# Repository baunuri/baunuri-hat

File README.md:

# Baunuri HAT

A robot controller board the size of a Raspberry Pi HAT (65 × 57 mm, the Pi's hole pattern and 40-pin header), built
around an ESP32-S3. It runs a robot on its own, or sits on a Pi when a robot needs more compute.

It was designed for [Popm](https://baunuri.com/popm/) and now also runs [XL-Duck](https://baunuri.com/xlduck/), whose
trained walking network runs on the ESP32-S3 itself. More: [baunuri.com/hat](https://baunuri.com/hat/).

## On the board
- **MCU:** ESP32-S3-WROOM-1-N16R8 (16 MB flash, 8 MB PSRAM), native USB-C for flashing and logs
- **Servos:** two half-duplex TTL servo bus plugs (Feetech STS3215 pinout), powered straight from the battery
- **RS485** (SP3485, UART0, DE on a GPIO) and **CAN** (SN65HVD230), each with a terminator behind a solder jumper
- **IMU:** LSM6DS3TR-C
- **Sound:** MAX98357A I2S amp, speaker plug
- **microSD** (SPI), **TCA9555** 16-bit I/O expander, two I2C buses (sensor plugs, ToF plug, Qwiic)
- **Power:** 2S–4S battery in (XT30), reverse-polarity FET, fuse, TVS; 5.4 V / 2 A buck, 3.3 V LDO; battery voltage sense
- **Pi header:** UART to the Pi, the Pi can reset the ESP32 or put it into its bootloader; the Pi's 5 V can run the logic,
  the battery never feeds the Pi

Full spec, pin map, power budget and design notes: [`pcb/README.md`](pcb/README.md). Pin map in code:
[`firmware/hat_bringup/board_hat.h`](firmware/hat_bringup/board_hat.h).

## Status
**Rev A**, ordered assembled from JLCPCB in November 2026 and brought up: the bring-up sketch
(`firmware/hat_bringup/`) tests each part over USB. An STS3215 runs on the servo bus at 1 Mbps (position within ~0.4°,
286°/s peak once its acceleration limit, register 85, is raised from the factory 50). XL-Duck's servos run on the RS485
port at 1 Mbps.

## Files
| Path | What |
|---|---|
| `pcb/popm_board.py` | the schematic, as code ([SKiDL](https://github.com/devbisme/skidl)) → netlist |
| `pcb/popm_board.kicad_pcb` | the layout (KiCad 9) |
| `pcb/layout.py`, `route.py`, `stitch.py`, `silk.py`, … | placement / routing / stitching / silkscreen scripts |
| `pcb/fab/` | what was ordered: Gerbers (zip), BOM and placement (CPL) for JLCPCB assembly, schematic PDF |
| `firmware/hat_bringup/` | the pin map (`board_hat.h`) and a bring-up sketch (Arduino, ESP32 core) |

## Making one
Upload `pcb/fab/popm_gerbers.zip` to JLCPCB with `popm_bom.csv` and `popm_cpl.csv` for assembly. **4 layers, 1.6 mm,
1 oz outer and 1 oz inner copper** (not the 0.5 oz inner default). The 2 × 20 Pi socket (J13) isn't in the BOM: solder a
tall stacking header yourself if you'll use a Pi. Check the notes in `pcb/README.md` ("Check by hand") first.

Or get a ready-made one: see [baunuri.com/hat](https://baunuri.com/hat/#get-one).

## Licenses
- **Hardware** (`pcb/`): [CERN-OHL-S-2.0](LICENSE), strongly reciprocal: if you make and distribute a modified board,
  publish its design files under the same licence.
- **Firmware** (`firmware/`): [MIT](firmware/LICENSE).
- **Documentation and images:** [CC BY 4.0](LICENSE-docs).

"Baunuri" and "Baunuri HAT" are names, not covered by these licences: boards you make from these files are welcome, but
please don't sell them under those names.

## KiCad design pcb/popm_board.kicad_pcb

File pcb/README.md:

# Design notes: Baunuri HAT rev A (POPM-HAT)

The board: the same circuits as the 74 × 38 POPM-CTRL, on a Raspberry Pi HAT-size board (65 × 57 mm, the Pi's
hole pattern) with a Pi-style 2 × 20 header (HATs plug onto it), a microSD on SPI and a 16-bit I2C GPIO expander.

One board instead of the Waveshare ESP32 servo board, the GY-521, the MAX98357A breakout, the buck converter and the
charge diode. It also adds a connector for the 8×8 ToF sensor.

**Status:** schematic as code (`popm_board.py`, SKiDL; ERC clean, 81 nets, 120 parts), placed, routed and through the
fab gate (`fab.py`); reviewed; ordered from JLCPCB (assembled) on 2026-11-10 at commit a57b8a4.

    cd pcb && python3 -m venv .venv && .venv/bin/pip install skidl   # once; needs KiCad 9's libraries
    .venv/bin/python popm_board.py                                    # -> popm_board.net (import it in Pcbnew)

## Fit
- **Outline:** 65 × 57 mm, rounded corners (R 3). 4 × 3.0 mm NPTH holes (M2.5) at (3.5, 4), (61.5, 4), (3.5, 53), (61.5, 53)
  from the top-left corner: a 58 × 49 mm rectangle, as on a Pi / HAT. No copper within 3.0 mm of a hole's centre, either side
  (screw heads, standoffs). 4 layers, 1.6 mm: F / In1 (solid GND) / In2 (signals) / B.
- **Order:** 4 layers, 1.6 mm, 1 oz outer **and 1 oz inner copper** (not JLC's 0.5 oz inner default: the battery trunk may run on the inner layer). Assemble 2, everything included: JLC solders the through-hole plugs too (`HAND=1` leaves them off and writes an LCSC cart instead).
- **Edges:** top: the Pi header (female, underneath). Left: the ESP32-S3's antenna over a notch (no copper beside it). Bottom: USB-C, I2C_B1, I2C_B2, QWIIC, TOF
  (JST-SH mouths at the edge). Right: BATTERY (XT30), UART (JST-SH), microSD slot. SERVO1/2 and SPEAKER are
  vertical plugs inside.
- **Stack height on a Pi 5:** use a tall stacking header with 15-16 mm (or taller) spacers. On a standard 8.5 mm or a low-profile socket the microSD card and the XT30 lead run into the Pi 5's Ethernet / USB jacks (review, from the Pi 5 drawing).
- **On a Pi:** this board is a HAT: it plugs onto a Raspberry Pi's 40-pin header with a female 2 × 20 socket underneath,
  and its holes line up with the Pi's (M2.5 standoffs). The socket's height sets the gap: underside parts and the plugs'
  through-hole pins (~2–3 mm) must clear the Pi's own parts (not checked against any Pi model).

## Pi header (J13, 2 × 20, 2.54 mm, female, underneath). Each pad right over the Pi's pin: rows at y 4 ± 1.27, pin 1 inside, at the left end
**Not assembled by JLC:** solder a tall 2 × 20 stacking header (2.54 mm, female, for 15-16 mm spacers on a Pi 5) yourself, from underneath (fab.py leaves J13 off the order).
The Pi and the ESP32 never drive the same line: everything else on the header is left open.
| Pi pin | Pi name | Net | This board |
|---|---|---|---|
| 2, 4 | 5V | PI_5V | into our +5V through a Schottky (D8): the Pi can run the ESP side; our battery never feeds the Pi |
| 6, 9, 14, 20, 25, 30, 34, 39 | GND | GND | |
| 8 | TXD (Pi out) | PI_TXD → 1k → UART_RX | ESP GPIO40 (UART2 RX) |
| 10 | RXD (Pi in) | UART_TX → 1k → PI_RXD | ESP GPIO39 (UART2 TX) |
| 11 | GPIO17 | PI_EN → 2N7002 (Q3) → ESP EN | Pi high = ESP held in reset |
| 13 | GPIO27 | PI_BOOT → 2N7002 (Q4) → ESP GPIO0 | Pi high = ESP boots into download mode (with a reset) |
| 7, 15, 16, 18, 22, 26, 29, 31 | | EXP_P00 … EXP_P07 (expander port 0, in that order) | |
| 32, 33, 36, 37 | | EXP_P10 … EXP_P13 (expander port 1) | |
| 1, 17 (3V3), 3, 5 (I2C), 27, 28 (ID EEPROM), 12, 35, 38, 40 (PCM), 19, 21, 23, 24 (SPI) | | not connected | |

- **UART2 is shared with the UART plug (J12):** use the Pi link or a device on the plug, not both (two TX outputs on one RX).
  The 1k resistors stop either side back-powering the other while it's off.
- **Reset / boot from the Pi:** the FETs (100k gate pull-downs; the Pi's GPIO17 / 27 also pull down at boot) stay off while the
  Pi is off or booting. Flash the ESP from the Pi over a USB-C cable (its ROM loader's UART is UART0, the RS485 one).
- **The 12 expander lines** come up as inputs on both sides (TCA9555 and the Pi): set directions in software before driving any.

## GPIO expander (U9, TCA9555PWR, LCSC C465732)
- On I2C bus A (I2C_A_SDA / I2C_A_SCL) at **0x20** (A0-A2 to GND; the IMU is 0x6A, the ToF 0x29). 3V3, 100 nF at VCC.
- P00-P07 and P10-P13 go to the header (table above). P14 / P15: AUX_EN / AUX_BOOT (UART plug; Pi pins 11 / 13 are PI_EN / PI_BOOT: the Pi resets / boot-selects the ESP), P16: the ToF's LPn, P17: test pad TP8.
- **INT is not wired to the ESP32** (no free GPIO): it has a 10k pull-up and test pad TP9. Firmware polls the input registers.

## microSD (J14, Molex 104031-0811, LCSC C585350), SPI mode
- DAT3/CS → SD_CS (GPIO 13), CMD → SPI_MOSI (38), CLK → SPI_SCK (21), DAT0 → SPI_MISO (47). 10k pull-ups to 3V3 on CS, CMD,
  DAT0, DAT1, DAT2; 10 µF + 100 nF at VDD. The card-detect switch isn't wired.
- Slot at the right edge. It's a push-pull socket (the card slides in and is pulled out), not push-push.

## CAN (U10, SN65HVD230, LCSC C12084) and RS485 (U11, SP3485EN, LCSC C8963)
- **CAN:** the ESP32-S3's TWAI on GPIO 41 (TX → D) / 42 (RX ← R). Rs to GND (full speed). 10k pull-up on TX: recessive
  through reset. Plug J15 (JST-GH 4, DroneCAN order): 1 +5V, 2 CANH, 3 CANL, 4 GND.
- **RS485:** UART0 (GPIO 43 TX → DI, 44 RX ← RO; the console is on USB), DE + /RE together on GPIO 8 (high = send), 10k
  pull-down: receiving through reset, so the boot log never reaches the bus. Plug J16 (JST-GH 4): 1 +5V, 2 A, 3 B, 4 GND.
- Each: a 120R terminator behind a solder jumper (JP1 CAN, JP2 RS485: bridge it on the boards at the bus's two ends) and a
  TVS (PESD2CAN, SM712). No RS485 fail-safe bias resistors: add them on the bus if nothing else biases it.

## Blocks
```
 2S–4S pack ───────────── reverse-polarity P-FET ─ fuse ─ TVS ─┬─ VBAT ── 2 × servo bus connectors (STS3215 chains)
                   │                                      └─ buck 5.4 V / 2 A ─ SS34 ─┬─ +5 V ── amp, XIAO, LED
                                                               USB-C VBUS ─ SS34 ──────┘    └─ AMS1117 ── +3V3: ESP32-S3, IMU, eyes, ToF, buffer
 (no switch, no charge port: in the pack's own lead)           VBAT divider ─▶ ADC

 ESP32-S3-WROOM-1-N16R8 ── UART1 ── 74LVC2G241 (DIR) ── servo bus (half duplex)
                        ── I2C bus B (up to 1 MHz) ── I2C_B1, I2C_B2 plugs, e.g. displays (JST-SH 4)
                        ── I2C bus A (400 kHz max) ── IMU + expander on board, ToF (JST-SH 6), Qwiic (JST-SH 4)
                        ── I2S ── MAX98357A ── speaker (JST-PH 2)
                        ── UART2 + EN/BOOT ── XIAO camera (JST-SH 6)
                        ── USB-C (native USB: flash + log, 5 V for the logic on the bench)
                        ── red status LED (GPIO48, high = on), BOOT button (doubles as a user button)
```

## Parts (LCSC numbers to fill in while drawing the schematic: prefer JLC basic / preferred parts)
| Block | Part | Why |
|---|---|---|
| MCU | ESP32-S3-WROOM-1-N16R8 | 16 MB flash (no more 97 %), 8 MB PSRAM, native USB, 2 I2C, 3 UARTs, I2S |
| Servo bus | 74LVC2G241 at 3.3 V + 10 k pull-up | half duplex with one DIR pin (the Robotis circuit). LVC inputs take 5 V, so a 5 V bus is safe on RX |
| IMU | LSM6DS3TR-C (or BMI270) | the MPU-6050 is end-of-life and clones vary; this one is cheap and stocked at JLC. Firmware: new register map |
| Amp | MAX98357AETE+ | same as now; SD_MODE on a GPIO (mute with no pop, save power) |
| 5 V buck | TPS54202 (4.5–28 V in, 2 A), set to 5.4 V, then an SS34 Schottky OR with USB 5 V | headroom over 12.6 V and charger spikes; USB powers the logic on the bench |
| 3.3 V | AMS1117-3.3 from 5 V | the average draw is ~0.2 A (Wi-Fi peaks are short); a second buck if it runs hot |
| Reverse polarity | P-FET, 30 V, ≥ 8 A (AO4407-class) | the pack plugged in backwards |
| Protection | 5 A / 30 V PTC fuse, SMBJ18A TVS on VBAT, USBLC6-2 on USB | rated for a full 4S (16.8 V); battery-side caps 35 V |
| Sense | VBAT 100 k / 18 k → ADC (16.8 V → 2.56 V) | battery % for the page |

## Pin map (ESP32-S3-WROOM-1-N16R8: GPIO 26–37 are taken by the octal flash and PSRAM)
| Function | GPIO |
|---|---|
| Servo TX / RX / DIR (UART1) | 17 / 18 / 16 |
| I2C bus B SDA / SCL (the two I2C_B plugs) | 4 / 5 |
| I2C bus A SDA / SCL (IMU, ToF, expander, Qwiic): **400 kHz max** (the TCA9555 and the IMU are Fast-mode parts) | 6 / 7 |
| IMU INT | 15 |
| ToF INT (LPn: expander P16) | 14 |
| I2S BCLK / LRC / DIN, amp SD | 10 / 11 / 12, 9 |
| VBAT sense (ADC1) | 1 (IO2 is free: it was the charger-present sense) |
| UART2 TX / RX (UART plug, Pi pins 10 / 8) | 39 / 40 |
| CAN TX / RX (TWAI) | 41 / 42 |
| RS485 TX / RX (UART0) / DE | 43 / 44 / 8 (enable GPIO44's pull-up: RO is high-Z while sending) |
| microSD: MOSI / MISO / SCK / CS | 38 / 47 / 21 / 13 |
| Status LED (red, through 1 k; high = on) | 48 |
| BOOT / user button | 0 |
| USB D− / D+ | 19 / 20 |
| Not connected (straps: JTAG select, flash voltage, ROM log) | 3, 45, 46 |
| On the expander: UART plug EN / BOOT, ToF LPn | P14 / P15, P16 (set the expander's outputs at boot: it keeps them through an ESP reset) |

## Connectors
| What | Connector | Pins |
|---|---|---|
| Battery in | XT30PW-M right angle (the pack's lead is an XT30 female) | pad 2 +, pad 1 − |

**No power switch and no charge port on the board** (as Waveshare's servo HAT): the board is live whenever a pack is
plugged in. Put a switch in the pack's lead if you want one, and charge the pack on its own charger, unplugged.

**The pack must be a protected one (it has a BMS: short-circuit, over-discharge, over-charge).** The board's 5 A fuse only
covers the board itself, and nothing on the board can stop the servos from running the cells flat.
| SERVO1, SERVO2: servo bus × 2 (e.g. a drive chain and a head chain) | Molex SPOX 5267-03A (the STS3215's own plug) | pin 1 DATA, 2 VBAT, 3 GND (as Waveshare's Bus Servo Adapter (A)) |
| I2C_B1, I2C_B2 | JST-SH 4 | 1 GND, 2 3V3, 3 SDA, 4 SCL (Qwiic order; bus B) |
| ToF | JST-SH 6 | 1 GND, 2 3V3, 3 SDA, 4 SCL, 5 LPn, 6 INT |
| Qwiic | JST-SH 4 | 1 GND, 2 3V3, 3 SDA, 4 SCL (bus A) |
| Speaker | JST-PH 2 | |
| UART (a co-processor, e.g. a XIAO camera) | JST-SH 6 | 1 GND, 2 5V, 3 TX, 4 RX, 5 EN, 6 BOOT (EN / BOOT from the expander: open drain by switching its direction) |
| USB-C | 16-pin receptacle | |

## Power budget
| Rail | Loads | Peak |
|---|---|---|
| VBAT (2S 6–8.4 V, 3S 9–12.6 V or 4S up to 16.8 V; the buck turns on above ~5.8 V) | servos straight off the pack, so match their version to it (STS3215 7.4 V on 2S, 12 V on 3S; 4S only with servos rated for it). Sense dividers 100k / 18k: 16.8 V reads 2.56 V. Bigger servo counts: power them from a separate hub, not through this board. Popm: 4 × STS3215 12 V (stall ~2.7 A each; driving 0.2–0.5 A each). Firmware torque limits keep stalls short | fuse 5 A hold, traces ≥ 5 A |
| 5 V | amp ~0.7 A at full volume, XIAO + camera ~0.3 A | ~1.0 A of 2 A (TPS54202), shared with everything on the 5 V plugs (CAN, RS485, UART) |
| 3.3 V | ESP32-S3 Wi-Fi ~0.5 A, ToF ~0.1 A, eyes 2 × 25 mA, IMU, buffer | ~0.2 A average (Wi-Fi peaks are short): an AMS1117 in SOT-223 can't sustain 0.7 A (~1.2 W) |

## 8×8 ToF (VL53L5CX family, ordered 2026-11-04)
- **Connector:** on the sensor I2C bus, not the eyes' (those send ~1 KB frames all the time). Bus A runs at 400 kHz max (the expander and the IMU on it).
- **LPn on a GPIO:** it can be reset, or moved off its default address if a second one is added.
- **Firmware:** its driver uploads ~86 KB of sensor firmware over I2C at every boot (~90 KB of flash): fine with 16 MB.
- **Placement:** probably the chest next to the camera, looking forward and a little down. CAD to follow when it arrives
  (measure the breakout: SparkFun / Pimoroni / generic).

## XIAO link (camera, mic)
- **Wires:** UART2 at 2 Mbps (both ends are S3s), plus the XIAO's EN (reset) and BOOT (GPIO0), driven open-drain by the main S3.
- **Messages:** short text lines, as the drive firmware already does on Serial: from the XIAO `face x y size`,
  `motion`, `loud`; to it `cam on/off`, `snap`. Small, easy to log, and a future brain can listen in.
- **Updating the XIAO through Popm:** the main S3 holds BOOT low and pulses EN to put the XIAO in its ROM bootloader, then
  streams a new XIAO firmware over the same UART (the esptool protocol, ESP's serial-flasher library). One update
  from the phone then covers both chips, with no USB cable into the chest.
- **Power:** 5 V from the board's buck, so the XIAO is reset with the robot. Optionally a load switch on a GPIO to turn the
  camera off when it isn't needed (saves ~0.3 A).
- **Pictures:** UART is enough for events and the odd still photo (a 20 KB JPEG in ~0.1 s). A live video stream should come
  straight from the XIAO's own Wi-Fi, joined to Popm's network, not through the main board.

## 5 V buck: checked against the TPS54202 datasheet (its SPICE model is encrypted: TI's tools only)
- Output: 0.596 V × (1 + 82k / 10k) = 5.48 V.
- Crossover (datasheet eq. 14): fo ≈ 3.95 / (Vout × Cout) = 3.95 / (5.48 V × ~40 µF) ≈ 18 kHz, under the 40 kHz limit.
  Cout: 3 × 22 µF 0805, ~13 µF each at 5.5 V bias.
- Feed-forward cap (eq. 16): 1 / (2π × 18 kHz × 82 kΩ) ≈ 108 pF → 100 pF.
- Inductor: 15 µH, as Table 7-2 for 5 V. Near 90 % duty (2S, nearly flat) a peak-current-mode buck leans on its slope
  compensation; 10 µH thinned that margin. Ripple 0.5 A at 16.8 V in; peak ~2 A at the rail's ~1.7 A, under 2.7 A sat.

## Check by hand before ordering
- **Servo plug pin order:** pin 1 DATA, 2 VBAT, 3 GND, taken from Waveshare's Bus Servo Adapter (A) schematic. Worth a
  multimeter check on a real lead (black wire = GND) against the plug's latch side before the first power-up.
- **STS3215 bus level:** the buffer drives 3.3 V. If the servos' input wants a 5 V high, a 5 V buffer is needed. Nothing gets
  damaged either way (the buffer's inputs and its off outputs take 5 V).
- **ToF breakout pinout** against the TOF connector, and whether the XIAO's EN / BOOT are reachable on its pads.
- **USB-only power:** VBUS minus the Schottky leaves ~4.3 V for the AMS1117 (dropout ~1.1 V): Wi-Fi peaks may brown out
  the S3 on the bench without the battery. On the battery (5.4 V buck) it's fine.

## Open questions
- **Servos:** decided 2026-11-04: Feetech STS3215, 12 V version (bought). Firmware needs the Feetech SCS/STS protocol
  (1 Mbps; position, speed and load registers) in place of Dynamixel 2.0.
- **Camera on the board:** fold the camera into the S3 (DVP camera connector) and drop the XIAO? Probably not: the camera
  is in the chest, the board is at the back, and a DVP flex cable that long is fragile.

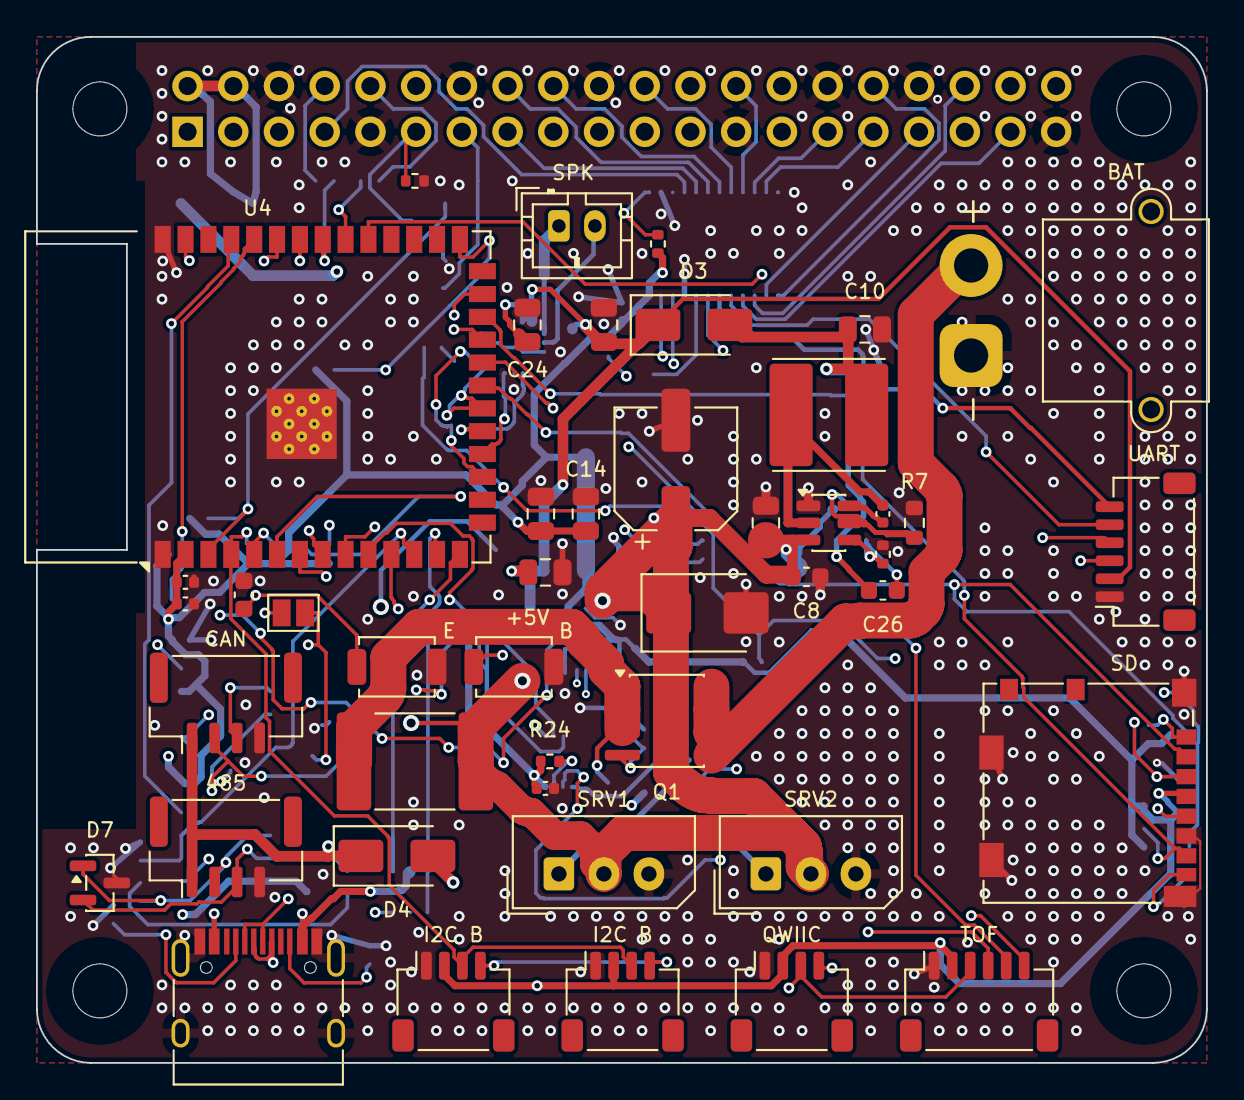
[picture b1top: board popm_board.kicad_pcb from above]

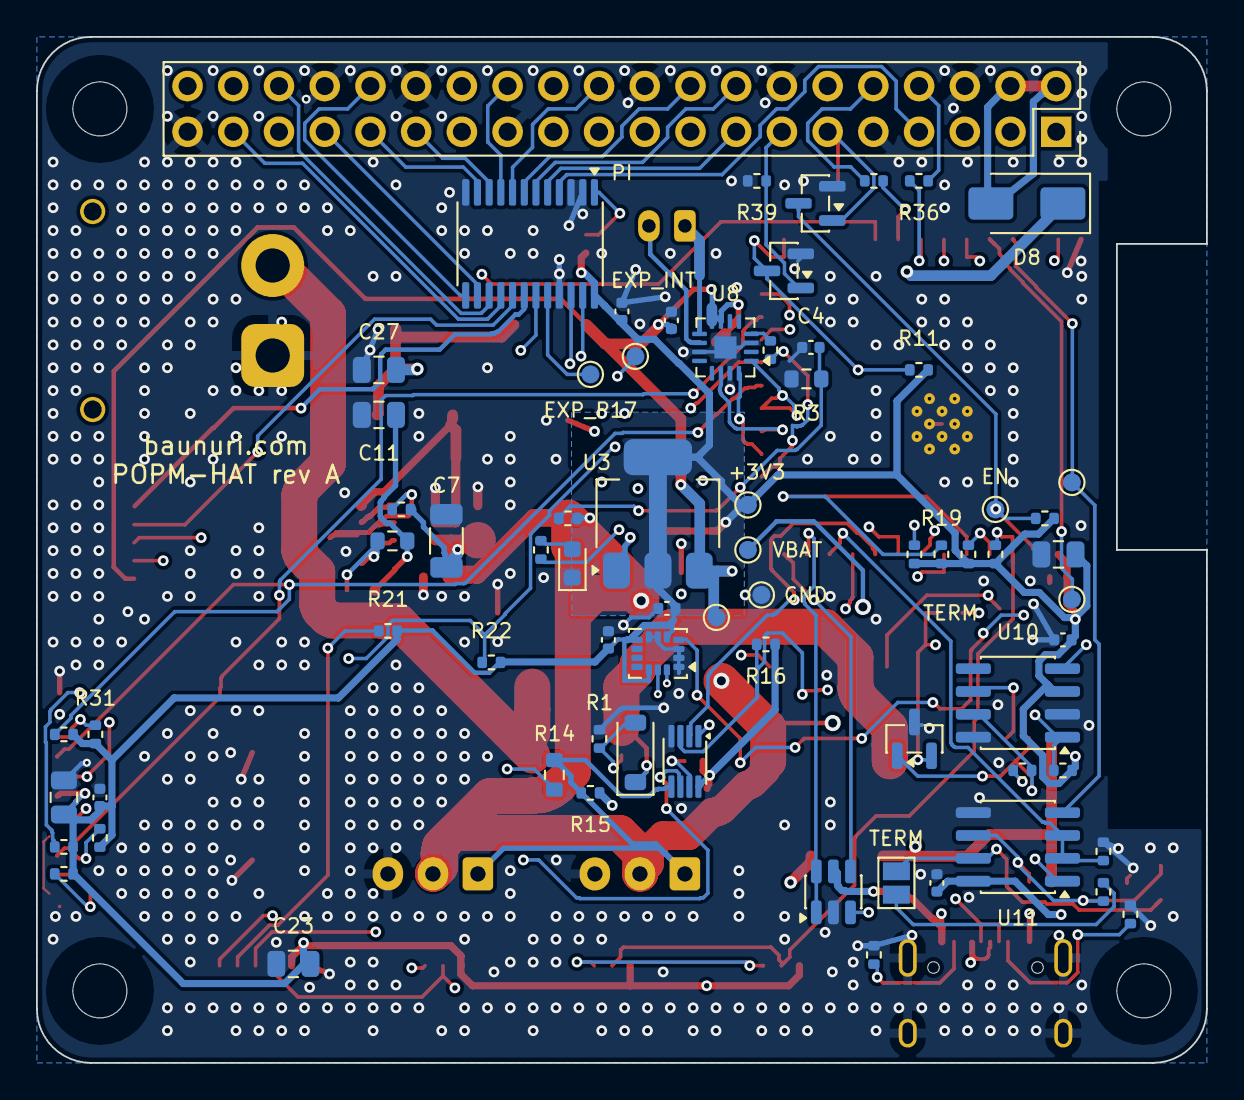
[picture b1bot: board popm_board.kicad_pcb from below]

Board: 4 copper layers, 65.0 x 57.0 mm, 120 parts (71 on the bottom side), 81 nets.

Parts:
C1: 100u 35V; CP_Elec_6.3x7.7
C4, C9, C17, C18, C20, C21, C22, C25, C28, C30, C31, C32: 100n; C_0402_1005Metric
C6, C16, C23, C24, C29: 10u; C_0805_2012Metric
C7: 10u; C_1206_3216Metric
C8: 100n; C_0603_1608Metric
C10, C11, C12, C13, C14, C15, C27: 22u; C_0805_2012Metric
C19: 1u; C_0603_1608Metric
C26: 100p; C_0603_1608Metric
D1: BZT52C12; D_SOD-123
D2: SMBJ18A; D_SMB
D3, D4, D8: SS34; D_SMA
D5: red; LED_0603_1608Metric
D6: PESD2CAN; SOT-23
D7: SM712; SOT-23
F1: 5A hold 30V; Fuse_2920_7451Metric
H1, H2, H3, H4: MountingHole; MountingHole_3mm
J1: BAT; AMASS_XT30PW-M_1x02_P2.50mm_Horizontal
J4: USB; USB_C_Receptacle_HRO_TYPE-C-31-M-12
J5: SRV1; Molex_SPOX_5267-03A_1x03_P2.50mm_Vertical
J6: SRV2; Molex_SPOX_5267-03A_1x03_P2.50mm_Vertical
J7, J8: I2C B; JST_SH_SM04B-SRSS-TB_1x04-1MP_P1.00mm_Horizontal
J9: TOF; JST_SH_SM06B-SRSS-TB_1x06-1MP_P1.00mm_Horizontal
J10: QWIIC; JST_SH_SM04B-SRSS-TB_1x04-1MP_P1.00mm_Horizontal
J11: SPK; JST_PH_B2B-PH-K_1x02_P2.00mm_Vertical
J12: UART; JST_SH_SM06B-SRSS-TB_1x06-1MP_P1.00mm_Horizontal
J13: PI; PinSocket_2x20_P2.54mm_Vertical
J14: SD; microSD_HC_Molex_104031-0811
J15: CAN; JST_GH_BM04B-GHS-TBT_1x04-1MP_P1.25mm_Vertical
J16: 485; JST_GH_BM04B-GHS-TBT_1x04-1MP_P1.25mm_Vertical
JP1, JP2: TERM; SolderJumper-2_P1.3mm_Open_Pad1.0x1.5mm
L1: 15u; L_Cenker_CKCS6045
Q1: AO4407A; SOIC-8_3.9x4.9mm_P1.27mm
Q3, Q4: 2N7002; SOT-23
R1, R9, R10, R11, R15, R16, R21, R22, R23, R24, R26, R27, R28, R29, R30, R31, R32, R33: 10k; R_0402_1005Metric
R2, R38, R39: 100k; R_0402_1005Metric
R3: 18k; R_0603_1608Metric
R6: 330k; R_0402_1005Metric
R7, R8: 82k; R_0603_1608Metric
R12, R13: 5.1k; R_0402_1005Metric
R14: 47; R_0603_1608Metric
R17, R18: 1.5k; R_0402_1005Metric
R19, R20: 2.2k; R_0402_1005Metric
R25, R36, R37: 1k; R_0402_1005Metric
R34, R35: 120; R_0402_1005Metric
SW1: E; SW_SPST_TS-1088-xR020
SW2: B; SW_SPST_TS-1088-xR020
TP1: RS485_TX; TestPoint_Pad_D1.0mm
TP2: RS485_RX; TestPoint_Pad_D1.0mm
TP3: GND; TestPoint_Pad_D1.0mm
TP4: +3V3; TestPoint_Pad_D1.0mm
TP5: VBAT; TestPoint_Pad_D1.0mm
TP6: +5V; TestPoint_Pad_D1.0mm
TP7: EN; TestPoint_Pad_D1.0mm
TP8: EXP_P17; TestPoint_Pad_D1.0mm
TP9: EXP_INT; TestPoint_Pad_D1.0mm
U2: TPS54202DDC; SOT-23-6
U3: AMS1117-3.3; SOT-223-3_TabPin2
U4: ESP32-S3-WROOM-1-N16R8; ESP32-S3-WROOM-1
U5: USBLC6-2SC6; SOT-23-6
U6: 74LVC2G241; VSSOP-8_2.3x2mm_P0.5mm
U7: LSM6DS3TR-C; LGA-14_3x2.5mm_P0.5mm_LayoutBorder3x4y
U8: MAX98357AETE+T; TQFN-16-1EP_3x3mm_P0.5mm_EP1.23x1.23mm
U9: TCA9555PWR; TSSOP-24_4.4x7.8mm_P0.65mm
U10: SN65HVD230; SOIC-8_3.9x4.9mm_P1.27mm
U11: SP3485EN; SOIC-8_3.9x4.9mm_P1.27mm

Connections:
+3V3: C14.1, C15.1, C16.1, C17.1, C18.1, C20.1, C21.1, C22.1, C23.1, C28.1, C29.1, C30.1, C31.1, C32.1, J7.2, J8.2, J9.2, J10.2, J14.4, R10.1, R11.1, R15.1, R16.1, R17.1, R18.1, R19.1, R20.1, R21.1, R22.1, R24.1, R26.1, R27.1, R28.1, R29.1, R30.1, R31.1, R32.1, TP4.1, U3.2, U4.2, U6.8, U7.5, U7.8, U7.12, U9.24, U10.3, U11.8
+5V: C12.1, C13.1, C24.1, C25.1, D3.1, D4.1, D8.1, J12.2, J15.1, J16.1, TP6.1, U3.3, U8.7, U8.8
+5V4: C10.1, C11.1, C26.1, C27.1, D3.2, L1.2, R8.1
AMP_SD: R23.1, U4.17
AUX_BOOT: J12.6, U9.18
AUX_EN: J12.5, U9.17
BAT_RAW: J1.2, Q1.5, Q1.6, Q1.7, Q1.8
BOOT: Q4.3, R11.2, SW2.1, U4.27
BUCK_BOOT: C9.1, U2.6
BUCK_EN: R6.2, R7.1, U2.5
BUCK_FB: C26.2, R8.2, R9.1, U2.4
BUCK_SW: C9.2, L1.1, U2.2
CANH: D6.1, J15.2, R34.1, U10.7
CANH_TERM: JP1.1, R34.2
CANL: D6.2, J15.3, JP1.2, U10.6
CAN_RX: U4.35, U10.4
CAN_TX: R32.2, U4.34, U10.1
EN: C19.1, Q3.3, R10.2, SW1.1, TP7.1, U4.3
EXP_INT: R26.2, TP9.1, U9.1
EXP_P00: J13.7, U9.4
EXP_P01: J13.15, U9.5
EXP_P02: J13.16, U9.6
EXP_P03: J13.18, U9.7
EXP_P04: J13.22, U9.8
EXP_P05: J13.26, U9.9
EXP_P06: J13.29, U9.10
EXP_P07: J13.31, U9.11
EXP_P10: J13.32, U9.13
EXP_P11: J13.33, U9.14
EXP_P12: J13.36, U9.15
EXP_P13: J13.37, U9.16
EXP_P17: TP8.1, U9.20
GND: C1.2, C4.2, C6.2, C7.2, C8.2, C10.2, C11.2, C12.2, C13.2, C14.2, C15.2, C16.2, C17.2, C18.2, C19.2, C20.2, C21.2, C22.2, C23.2, C24.2, C25.2, C27.2, C28.2, C29.2, C30.2, C31.2, C32.2, D2.2, D5.1, D6.3, D7.3, J1.1, J4.A1, J4.A12, J4.B1, J4.B12, J4.S1, J5.3, J6.3, J7.1, J8.1, J9.1, J10.1, J12.1, J13.6, J13.9, J13.14, J13.20, J13.25, J13.30, J13.34, J13.39, J14.6, J14.11, J15.4, J16.4, Q3.2, Q4.2, R1.2, R3.2, R7.2, R9.2, R12.2, R13.2, R33.2, R38.2, R39.2, SW1.2, SW2.2, TP3.1, U2.1, U3.1, U4.1, U4.40, U4.41, U5.2, U6.4, U7.1, U7.2, U7.3, U7.6, U7.7, U8.3, U8.11, U8.15, U8.17, U9.2, U9.3, U9.12, U9.21, U10.2, U10.8, U11.5
I2C_A_SCL: J9.4, J10.4, R20.2, U4.7, U7.13, U9.22
I2C_A_SDA: J9.3, J10.3, R19.2, U4.6, U7.14, U9.23
I2C_B_SCL: J7.4, J8.4, R18.2, U4.5
I2C_B_SDA: J7.3, J8.3, R17.2, U4.4
I2S_BCLK: U4.18, U8.16
I2S_DIN: U4.20, U8.1
I2S_LRC: U4.19, U8.14
IMU_INT: U4.8, U7.4
LED_A: D5.2, R25.2
unnamed: J4.A5, R12.1
unnamed: J4.B5, R13.1
unnamed: R23.2, U8.4
unnamed: R25.1, U4.25
PI_5V: D8.2, J13.2, J13.4
PI_BOOT: J13.13, Q4.1, R39.1
PI_EN: J13.11, Q3.1, R38.1
PI_RXD: J13.10, R37.2
PI_TXD: J13.8, R36.1
RP_GATE: D1.2, Q1.4, R1.1
RS485_A: D7.1, J16.2, R35.1, U11.6
RS485_A_TERM: JP2.1, R35.2
RS485_B: D7.2, J16.3, JP2.2, U11.7
RS485_DE: R33.1, U4.12, U11.2, U11.3
RS485_RX: TP2.1, U4.36, U11.1
RS485_TX: TP1.1, U4.37, U11.4
SD_CS: J14.2, R27.2, U4.21
SD_DAT1: J14.8, R30.2
SD_DAT2: J14.1, R31.2
SERVO_DATA: J5.1, J6.1, R14.2, R15.2, U6.5
SERVO_DIR: R24.2, U4.9, U6.1, U6.7
SERVO_DRV: R14.1, U6.6
SERVO_RX: R16.2, U4.11, U6.3
SERVO_TX: U4.10, U6.2
SPI_MISO: J14.7, R29.2, U4.24
SPI_MOSI: J14.3, R28.2, U4.31
SPI_SCK: J14.5, U4.23
SPK+: J11.1, U8.9
SPK-: J11.2, U8.10
TOF_INT: J9.6, R22.2, U4.22
TOF_LPN: J9.5, R21.2, U9.19
UART_RX: J12.4, R36.2, U4.33
UART_TX: J12.3, R37.1, U4.32
USB_D+: J4.A6, J4.B6, U4.14, U5.3, U5.4
USB_D-: J4.A7, J4.B7, U4.13, U5.1, U5.6
VBAT: C1.1, C6.1, C7.1, C8.1, D2.1, F1.2, J5.2, J6.2, R2.1, R6.1, TP5.1, U2.3
VBAT_FET: D1.1, F1.1, Q1.1, Q1.2, Q1.3
VBAT_SENSE: C4.1, R2.2, R3.1, U4.39
VBUS: D4.2, J4.A4, J4.A9, J4.B4, J4.B9, U5.5

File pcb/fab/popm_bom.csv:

Comment,Designator,Footprint,JLCPCB Part #
100u 35V,C1,CP_Elec_6.3x7.7,C72478
22u,"C11,C27,C10,C12,C13,C14,C15",C_0805_2012Metric,C45783
10u,"C16,C23,C29,C6,C24",C_0805_2012Metric,C15850
1u,C19,C_0603_1608Metric,C15849
100p,C26,C_0603_1608Metric,C14858
100n,"C4,C21,C22,C25,C28,C30,C31,C32,C9,C17,C18,C20",C_0402_1005Metric,C1525
10u,C7,C_1206_3216Metric,C13585
100n,C8,C_0603_1608Metric,C14663
BZT52C12,D1,D_SOD-123,C173429
SMBJ18A,D2,D_SMB,C151256
red,D5,LED_0603_1608Metric,C2286
PESD2CAN,D6,SOT-23,C75176
SM712,D7,SOT-23,C521963
SS34,"D8,D3,D4",D_SMA,C8678
5A hold 30V,F1,Fuse_2920_7451Metric,C19078763
BAT,J1,AMASS_XT30PW-M_1x02_P2.50mm_Horizontal,C431092
SPK,J11,JST_PH_B2B-PH-K_1x02_P2.00mm_Vertical,C131337
SD,J14,microSD_HC_Molex_104031-0811,C585350
485 / CAN,"J15,J16",JST_GH_BM04B-GHS-TBT_1x04-1MP_P1.25mm_Vertical,C161692
USB,J4,USB_C_Receptacle_HRO_TYPE-C-31-M-12,C165948
SRV1 / SRV2,"J5,J6",Molex_SPOX_5267-03A_1x03_P2.50mm_Vertical,C293315
I2C B / QWIIC,"J7,J8,J10",JST_SH_SM04B-SRSS-TB_1x04-1MP_P1.00mm_Horizontal,C160404
TOF / UART,"J9,J12",JST_SH_SM06B-SRSS-TB_1x06-1MP_P1.00mm_Horizontal,C160405
15u,L1,L_Cenker_CKCS6045,C83374
AO4407A,Q1,SOIC-8_3.9x4.9mm_P1.27mm,C2841482
2N7002,"Q3,Q4",SOT-23,C8545
10k,"R1,R10,R11,R15,R16,R21,R22,R23,R27,R28,R29,R30,R31,R32,R33,R9,R24,R26",R_0402_1005Metric,C25744
5.1k,"R12,R13",R_0402_1005Metric,C25905
47,R14,R_0603_1608Metric,C23182
1.5k,"R17,R18",R_0402_1005Metric,C25867
2.2k,"R19,R20",R_0402_1005Metric,C25879
100k,"R2,R39,R38",R_0402_1005Metric,C25741
1k,"R25,R36,R37",R_0402_1005Metric,C11702
18k,R3,R_0603_1608Metric,C25810
120,"R34,R35",R_0402_1005Metric,C25079
330k,R6,R_0402_1005Metric,C25778
82k,"R8,R7",R_0603_1608Metric,C23254
B / E,"SW1,SW2",SW_SPST_TS-1088-xR020,C720477
SN65HVD230,U10,SOIC-8_3.9x4.9mm_P1.27mm,C12084
SP3485EN,U11,SOIC-8_3.9x4.9mm_P1.27mm,C8963
TPS54202DDC,U2,SOT-23-6,C191884
AMS1117-3.3,U3,SOT-223-3_TabPin2,C6186
ESP32-S3-WROOM-1-N16R8,U4,ESP32-S3-WROOM-1,C2913202
USBLC6-2SC6,U5,SOT-23-6,C2687116
74LVC2G241,U6,VSSOP-8_2.3x2mm_P0.5mm,C10430
LSM6DS3TR-C,U7,LGA-14_3x2.5mm_P0.5mm_LayoutBorder3x4y,C967633
MAX98357AETE+T,U8,TQFN-16-1EP_3x3mm_P0.5mm_EP1.23x1.23mm,C910544
TCA9555PWR,U9,TSSOP-24_4.4x7.8mm_P0.65mm,C465732

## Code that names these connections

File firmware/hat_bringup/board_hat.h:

// POPM-HAT rev A (pcb/popm_board.py, branch pcb-no-sw-chg, ordered 2026-11-10): the ESP32-S3's pins and the I2C parts.
// The one place the pin numbers live: every sketch for this board includes this file.
#pragma once
#include <Arduino.h>
#include <Wire.h>

// servo bus: Feetech STS3215, half duplex through a 74LVC2G241, 1 Mbps. DIR low = transmit, high = receive
// (pulled up: receive through reset)
const int SERVO_TX = 17, SERVO_RX = 18, SERVO_DIR = 16;
// bus A (Wire): IMU, IO expander, ToF plug, Qwiic plug, Pi pins 3 / 5 are NOT on it. 2.2k pull-ups: 400 kHz at most
const int I2C_A_SDA = 6, I2C_A_SCL = 7;
const uint32_t I2C_A_HZ = 400000;
const uint8_t IMU_ADDR = 0x6A, EXP_ADDR = 0x20, TOF_ADDR = 0x29;   // LSM6DS3TR-C, TCA9555, VL53L5CX (if plugged in)
const int IMU_INT = 15, TOF_INT = 14;
// bus B (Wire1): nothing on the board; the two I2C_B plugs (the eyes). 1.5k pull-ups: up to 1 MHz
const int I2C_B_SDA = 4, I2C_B_SCL = 5;
// sound: MAX98357A. AMP_SD high = on, low = shutdown
const int I2S_BCLK = 10, I2S_LRC = 11, I2S_DIN = 12, AMP_SD = 9;
// microSD, SPI mode
const int SD_MOSI = 38, SD_MISO = 47, SD_SCK = 21, SD_CS = 13;
// CAN (TWAI) through an SN65HVD230; RS485 (UART0) through an SP3485: DE high = transmit (its receiver is off then),
// low = receive (pulled down: receive through reset). RX floats while transmitting: keep its pull-up on
const int CAN_TX = 41, CAN_RX = 42;
const int RS485_TX = 43, RS485_RX = 44, RS485_DE = 8;
// UART plug, shared with the Pi's UART (Pi pins 8 / 10 through 1k): use one or the other
const int UART_TX = 39, UART_RX = 40;
// battery: 100k / 18k divider on ADC1. ponytail: nominal ratio; trim VBAT_TRIM against a multimeter on the real board
const int VBAT_ADC = 1;
const float VBAT_RATIO = (100.0f + 18.0f) / 18.0f, VBAT_TRIM = 1.0f;
const int LED = 48;                       // red, high = on
// free: IO2. Not usable: IO0 (BOOT button), IO3 / IO45 / IO46 (straps), IO19 / IO20 (USB), IO35-37 (the module's PSRAM)

// TCA9555 pins on port 1 (port 0 and P10-P13 go to the Pi header, P17 to a test pad)
const uint8_t EXP_AUX_EN = 1 << 4, EXP_AUX_BOOT = 1 << 5, EXP_TOF_LPN = 1 << 6;
enum { EXP_IN0 = 0, EXP_IN1, EXP_OUT0, EXP_OUT1, EXP_POL0, EXP_POL1, EXP_CFG0, EXP_CFG1 };   // its registers

inline bool i2cWrite(TwoWire& w, uint8_t addr, uint8_t reg, uint8_t v) {
  w.beginTransmission(addr); w.write(reg); w.write(v); return w.endTransmission() == 0;
}
inline int i2cRead(TwoWire& w, uint8_t addr, uint8_t reg) {   // -1: no answer
  w.beginTransmission(addr); w.write(reg);
  if (w.endTransmission(false) != 0 || w.requestFrom(addr, (uint8_t)1) != 1) return -1;
  return w.read();
}

// The expander keeps its registers through an ESP reset (only a power cycle clears them), so set them every boot:
// every pin an input (high-Z: the Pi may drive its 12 lines; the UART plug's EN / BOOT and the ToF's LPn sit on their
// pull-ups), output latches low for EN / BOOT (so making one an output pulls it low: open drain) and high for LPn.
inline bool expBegin() {
  return i2cWrite(Wire, EXP_ADDR, EXP_CFG0, 0xFF) && i2cWrite(Wire, EXP_ADDR, EXP_CFG1, 0xFF) &&
         i2cWrite(Wire, EXP_ADDR, EXP_OUT0, 0x00) && i2cWrite(Wire, EXP_ADDR, EXP_OUT1, EXP_TOF_LPN);
}
// pull one of the open-drain lines low (true) or let it go (false): expPull(EXP_AUX_EN, true) holds the co-processor in reset
inline bool expPull(uint8_t bit, bool low) {
  int c = i2cRead(Wire, EXP_ADDR, EXP_CFG1);
  return c >= 0 && i2cWrite(Wire, EXP_ADDR, EXP_CFG1, low ? (c & ~bit) : (c | bit));
}

inline float vbat() { return analogReadMilliVolts(VBAT_ADC) / 1000.0f * VBAT_RATIO * VBAT_TRIM; }

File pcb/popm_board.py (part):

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    conn(3, "Connector_Molex:Molex_SPOX_5267-03A_1x03_P2.50mm_Vertical", "C293315", [bus, vbat, gnd], name)

# ---- eye bus (I2C1, 1 MHz) -------------------------------------------------------------------------------------------
esda, escl = Net("I2C_B_SDA"), Net("I2C_B_SCL")   # bus B: nothing on board; two plugs + Pi pins 27 / 28 (was the displays')
u["IO4"] += esda; u["IO5"] += escl
R("1.5k", v3, esda); R("1.5k", v3, escl)
SH4 = "Connector_JST:JST_SH_SM04B-SRSS-TB_1x04-1MP_P1.00mm_Horizontal"
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    conn(4, SH4, "C160404", [gnd, v3, esda, escl], name)

# ---- sensor bus (I2C0): IMU, ToF, Qwiic spare -------------------------------------------------------------------------
ssda, sscl = Net("I2C_A_SDA"), Net("I2C_A_SCL")   # bus A: the IMU, ToF, expander on it; Qwiic + Pi pins 3 / 5
u["IO6"] += ssda; u["IO7"] += sscl
R("2.2k", v3, ssda); R("2.2k", v3, sscl)
imu = Part("Sensor_Motion", "LSM6DS3", value="LSM6DS3TR-C", LCSC="C967633")
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# ---- POPM-HAT (65 x 57, Raspberry Pi HAT size): a Pi-style 2 x 20 header, a microSD on SPI, a 16-bit I2C GPIO expander.
# Created last, so every part above keeps its number (layout.py maps refs).
spi_mosi, spi_miso, spi_sck, sd_cs = (Net(n) for n in ("SPI_MOSI", "SPI_MISO", "SPI_SCK", "SD_CS"))
u["IO38"] += spi_mosi; u["IO47"] += spi_miso; u["IO21"] += spi_sck; u["IO13"] += sd_cs   # CS: a right-side pin, by the slot
u["IO3"] += NC; u["IO46"] += NC                   # (were header-only: SPI CE0, I2S in; IO3 / IO46 are straps, left alone)
# Pi header: FEMALE, underneath: this board sits on a Raspberry Pi. Pin numbers are the Pi's, each pad right above the Pi's pin
# (odd row inside, even row on the edge). The Pi and the ESP never drive the same line: 3V3, I2C, SPI, I2S and the ID EEPROM
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exp_nets = {f"P{k}": Net(f"EXP_P{k}") for k in ("00 01 02 03 04 05 06 07 10 11 12 13 17".split())}
exp_nets |= {"P14": xen, "P15": xboot, "P16": tof_lpn}   # slow on / off lines moved off the ESP to free IO41 / 42 / 13 for CAN /
# RS485. The expander's pins come up as inputs (high-Z): the XIAO's EN / BOOT keep its own pull-ups, LPn its 10k (ToF on)
pi5, pi_tx, pi_rx, pi_en, pi_boot = (Net(n) for n in ("PI_5V", "PI_TXD", "PI_RXD", "PI_EN", "PI_BOOT"))
PI = {2: pi5, 4: pi5, 8: pi_tx, 10: pi_rx, 11: pi_en, 13: pi_boot}
for n in (1, 17, 3, 5, 27, 28, 12, 35, 38, 40, 19, 21, 23, 24): PI[n] = NC
for n in (6, 9, 14, 20, 25, 30, 34, 39): PI[n] = gnd
# the Pi's otherwise unused pins: the expander, port 0 then port 1 in order along the header
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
